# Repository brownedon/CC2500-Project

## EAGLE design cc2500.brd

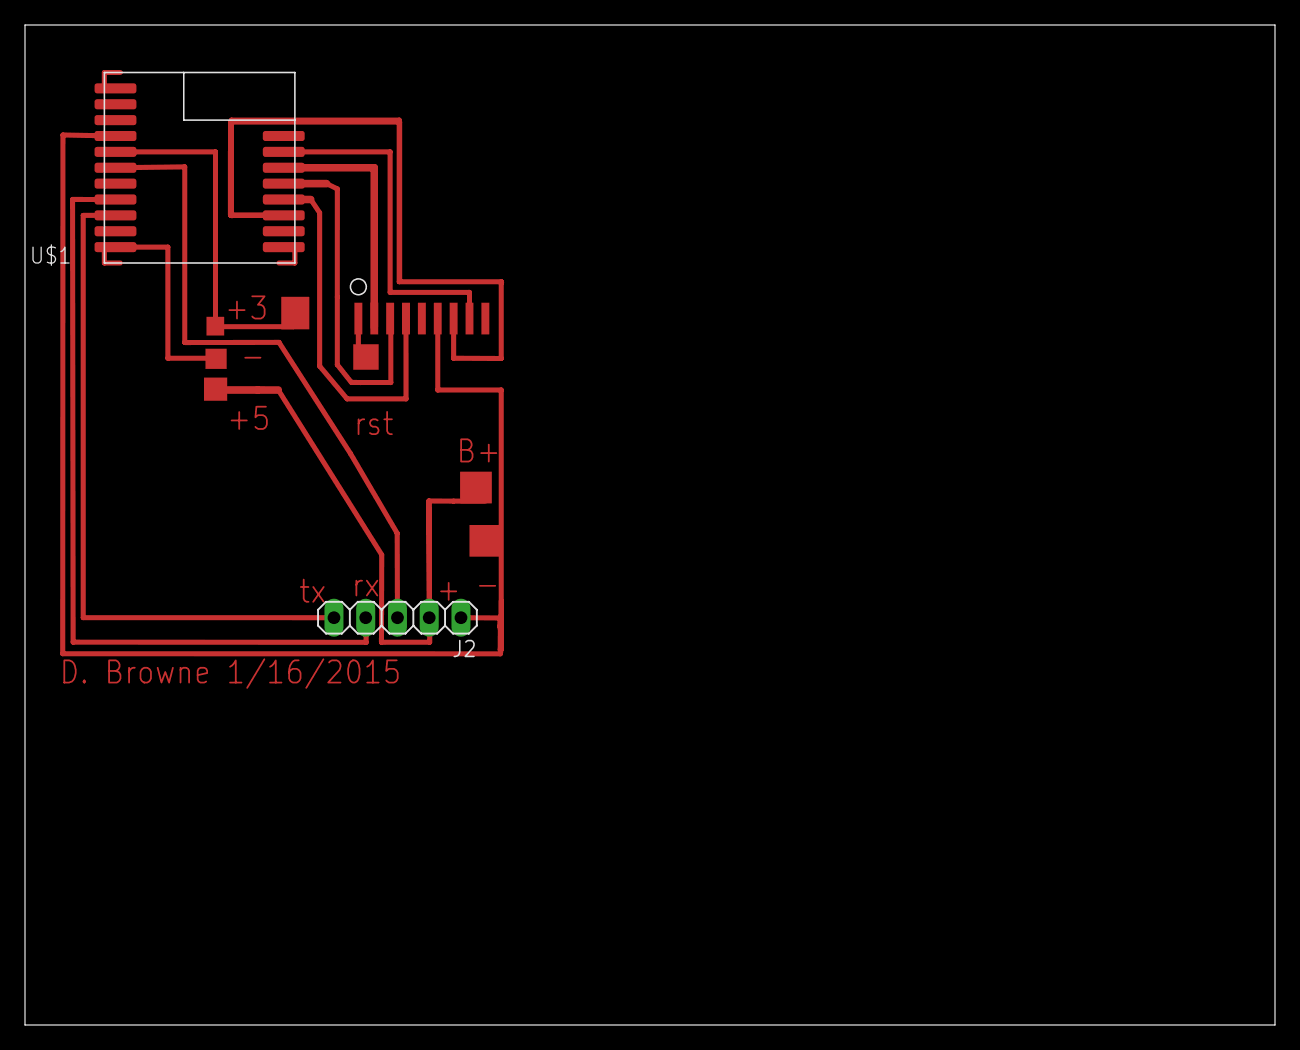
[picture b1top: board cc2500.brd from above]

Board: 2 copper layers, 100.0 x 80.0 mm, 3 parts (0 on the bottom side), 9 nets.

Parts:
J2: 1X05
U$1: RFD22301; RFD21733
U$2: CC2500-RADIO; CC2500BOARD

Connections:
unnamed: U$1.P$3, U$2.7
unnamed: J2.1, U$1.P$12, U$2.6
unnamed: J2.3, U$1.P$14
unnamed: U$1.P$7, U$2.8
unnamed: U$1.P$4, U$2.4
unnamed: U$1.P$5, U$2.3
unnamed: U$1.P$6, U$2.2
unnamed: J2.4, U$1.P$16
unnamed: J2.5, U$1.P$17

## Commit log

2015-04-10 First Commit
    CC2500 project, include arduino code, modified libraries, skp files for
    a case and a printed circuit layout for eagle.
2015-04-30 Added schematic
2015-07-10 CC2500 Updates
    Changes to cc2500 register settings for the new "skinny" transmitter....
